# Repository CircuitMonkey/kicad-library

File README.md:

# kicad-library
CircuitMonkey's Custom KiCAD Library

Replaces FUGLY and poorly implemented KiCAD standard library symbols and footprints.

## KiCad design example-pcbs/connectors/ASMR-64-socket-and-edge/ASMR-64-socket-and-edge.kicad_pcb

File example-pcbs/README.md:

# kicad-library - example PCBs
Test and Validation boards for parts in CircuitMonkey's Custom KiCAD Library

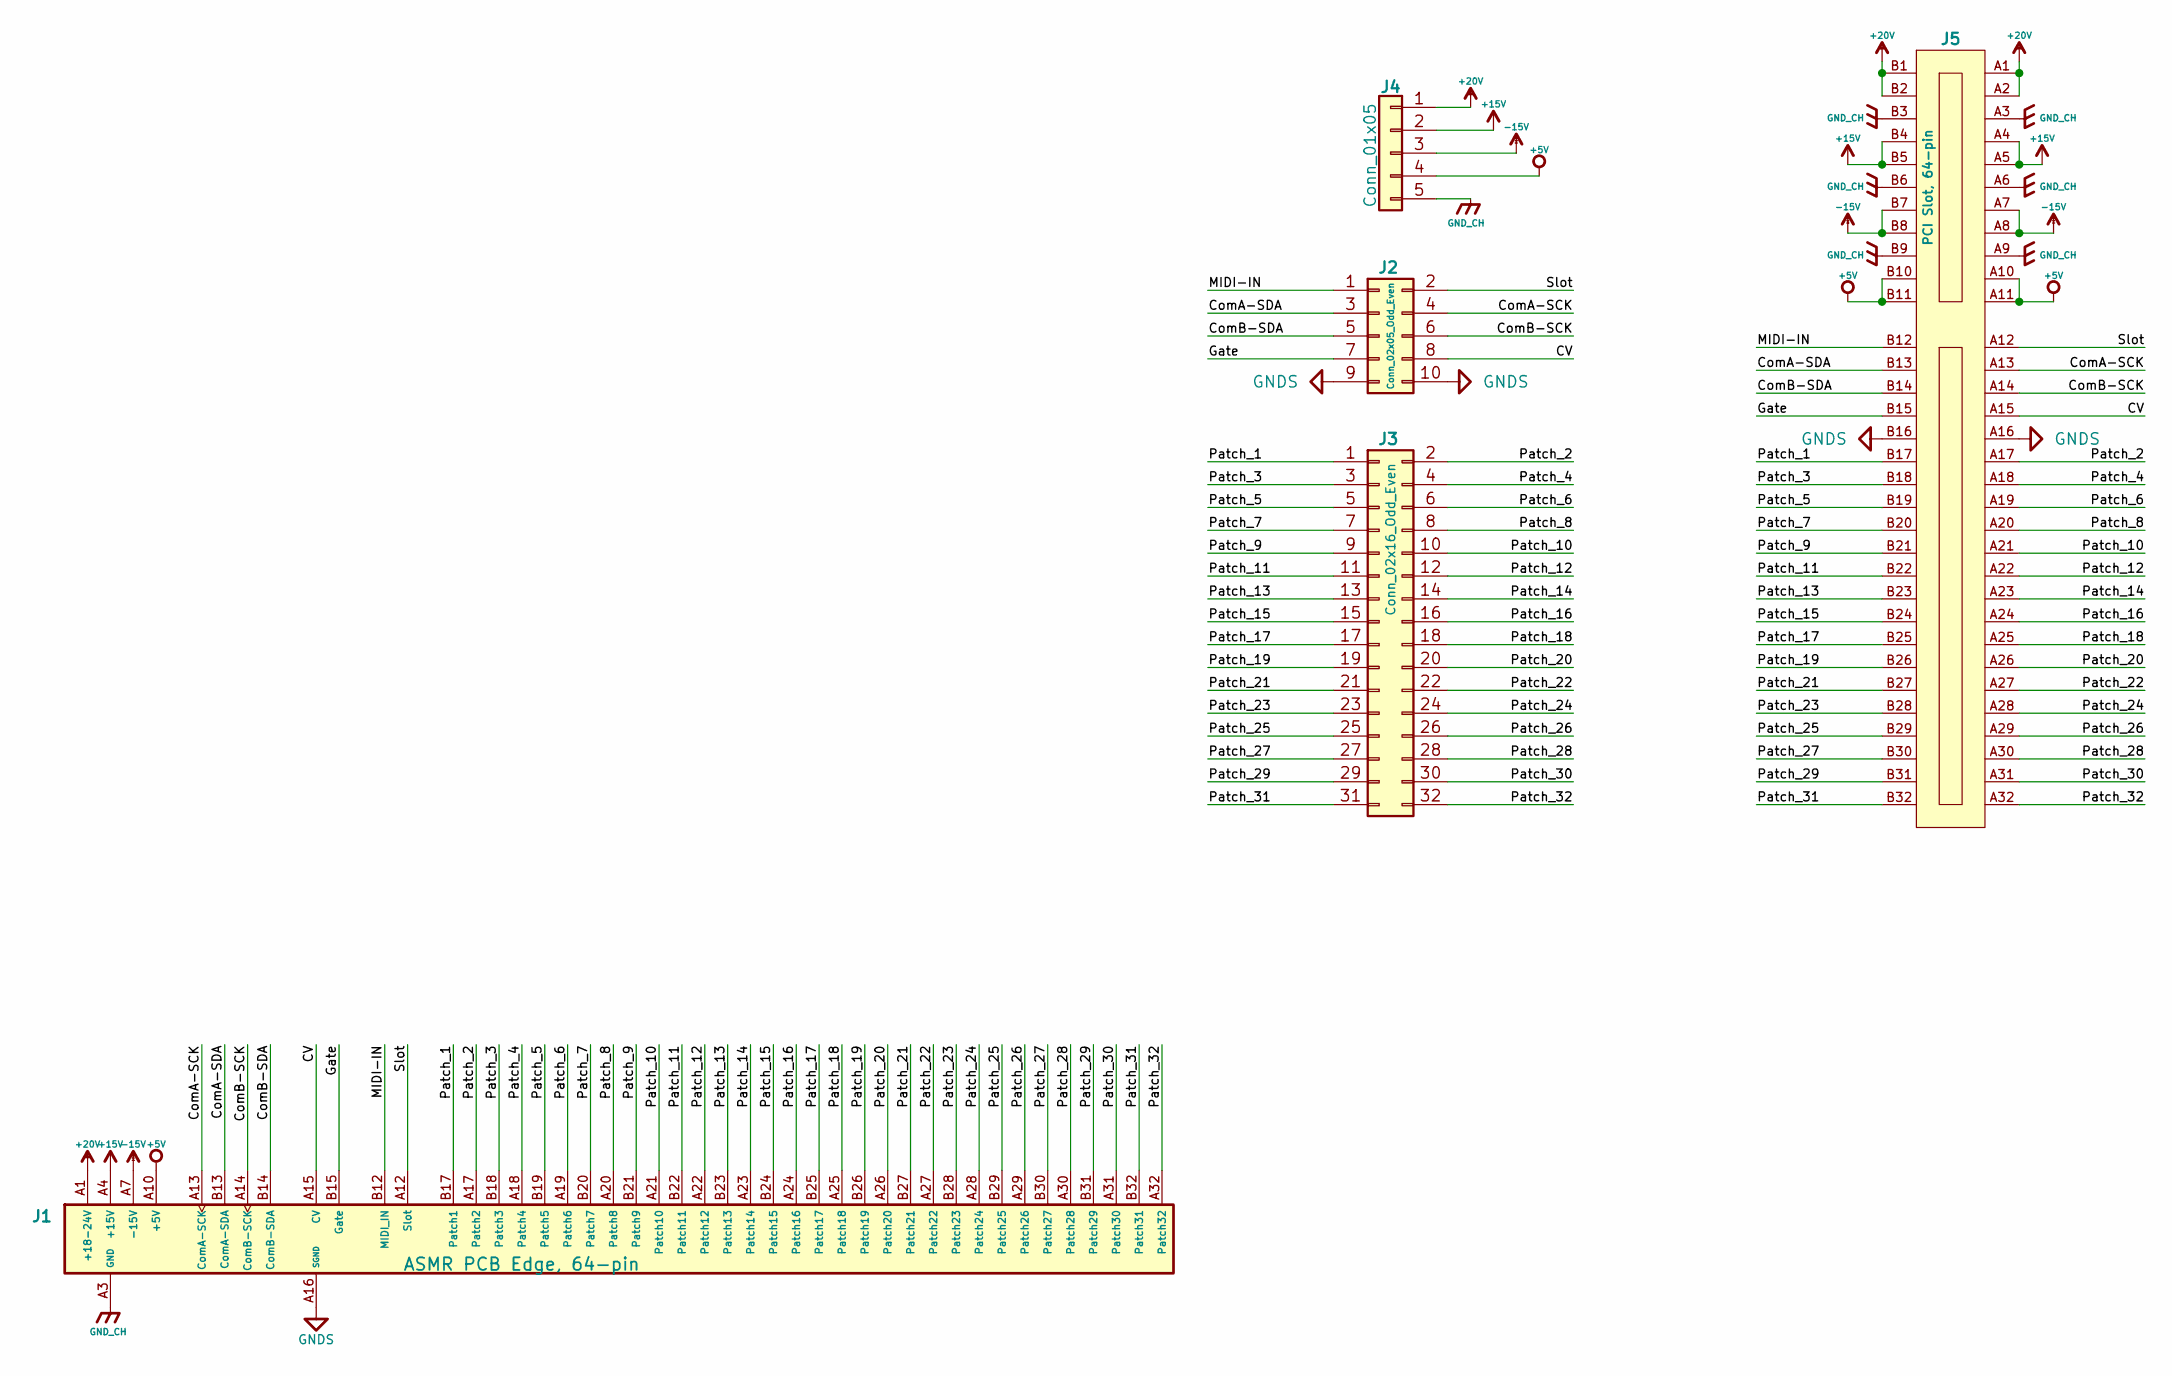
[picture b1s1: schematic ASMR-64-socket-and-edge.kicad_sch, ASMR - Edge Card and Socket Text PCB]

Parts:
J1: ASMR-Edge-64
J2: Conn_02x05_Odd_Even; PinHeader_2x05_P2.54mm_Vertical
J3: Conn_02x16_Odd_Even; PinHeader_2x16_P2.54mm_Vertical
J4: Conn_01x05; PinHeader_1x05_P2.54mm_Vertical
J5: PCI-Slot-64-THD-FCI-10018784; MPN 10018783-10201TLF

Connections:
+5V: J1.A10 (+5V), J1.A11 (+5V), J1.B10 (+5V), J1.B11 (+5V), J4.4, J5.A10, J5.A11, J5.B10, J5.B11
+15V: J1.A4 (+15V), J1.A5 (+15V), J1.B4 (+15V), J1.B5 (+15V), J4.2, J5.A4, J5.A5, J5.B4, J5.B5
+20V: J1.A1 (+18-24V), J1.A2 (+18-24V), J1.B1 (+18-24V), J1.B2 (+18-24V), J4.1, J5.A1, J5.A2, J5.B1, J5.B2
-15V: J1.A7 (-15V), J1.A8 (-15V), J1.B7 (-15V), J1.B8 (-15V), J4.3, J5.A7, J5.A8, J5.B7, J5.B8
/CV: J1.A15 (CV), J2.8, J5.A15
/ComA-SCK: J1.A13 (ComA-SCK), J2.4, J5.A13
/ComA-SDA: J1.B13 (ComA-SDA), J2.3, J5.B13
/ComB-SCK: J1.A14 (ComB-SCK), J2.6, J5.A14
/ComB-SDA: J1.B14 (ComB-SDA), J2.5, J5.B14
/Gate: J1.B15 (Gate), J2.7, J5.B15
/MIDI-IN: J1.B12 (MIDI_IN), J2.1, J5.B12
/Patch_1: J1.B17 (Patch1), J3.1, J5.B17
/Patch_2: J1.A17 (Patch2), J3.2, J5.A17
/Patch_3: J1.B18 (Patch3), J3.3, J5.B18
/Patch_4: J1.A18 (Patch4), J3.4, J5.A18
/Patch_5: J1.B19 (Patch5), J3.5, J5.B19
/Patch_6: J1.A19 (Patch6), J3.6, J5.A19
/Patch_7: J1.B20 (Patch7), J3.7, J5.B20
/Patch_8: J1.A20 (Patch8), J3.8, J5.A20
/Patch_9: J1.B21 (Patch9), J3.9, J5.B21
/Patch_10: J1.A21 (Patch10), J3.10, J5.A21
/Patch_11: J1.B22 (Patch11), J3.11, J5.B22
/Patch_12: J1.A22 (Patch12), J3.12, J5.A22
/Patch_13: J1.B23 (Patch13), J3.13, J5.B23
/Patch_14: J1.A23 (Patch14), J3.14, J5.A23
/Patch_15: J1.B24 (Patch15), J3.15, J5.B24
/Patch_16: J1.A24 (Patch16), J3.16, J5.A24
/Patch_17: J1.B25 (Patch17), J3.17, J5.B25
/Patch_18: J1.A25 (Patch18), J3.18, J5.A25
/Patch_19: J1.B26 (Patch19), J3.19, J5.B26
/Patch_20: J1.A26 (Patch20), J3.20, J5.A26
/Patch_21: J1.B27 (Patch21), J3.21, J5.B27
/Patch_22: J1.A27 (Patch22), J3.22, J5.A27
/Patch_23: J1.B28 (Patch23), J3.23, J5.B28
/Patch_24: J1.A28 (Patch24), J3.24, J5.A28
/Patch_25: J1.B29 (Patch25), J3.25, J5.B29
/Patch_26: J1.A29 (Patch26), J3.26, J5.A29
/Patch_27: J1.B30 (Patch27), J3.27, J5.B30
/Patch_28: J1.A30 (Patch28), J3.28, J5.A30
/Patch_29: J1.B31 (Patch29), J3.29, J5.B31
/Patch_30: J1.A31 (Patch30), J3.30, J5.A31
/Patch_31: J1.B32 (Patch31), J3.31, J5.B32
/Patch_32: J1.A32 (Patch32), J3.32, J5.A32
/Slot: J1.A12 (Slot), J2.2, J5.A12
GNDS: J1.A16 (SGND), J1.B16 (SGND), J2.9, J2.10, J5.A16, J5.B16
GND_CH: J1.A3 (GND), J1.A6 (GND), J1.A9 (GND), J1.B3 (GND), J1.B6 (GND), J1.B9 (GND), J4.5, J5.A3, J5.A6, J5.A9, J5.B3, J5.B6, J5.B9

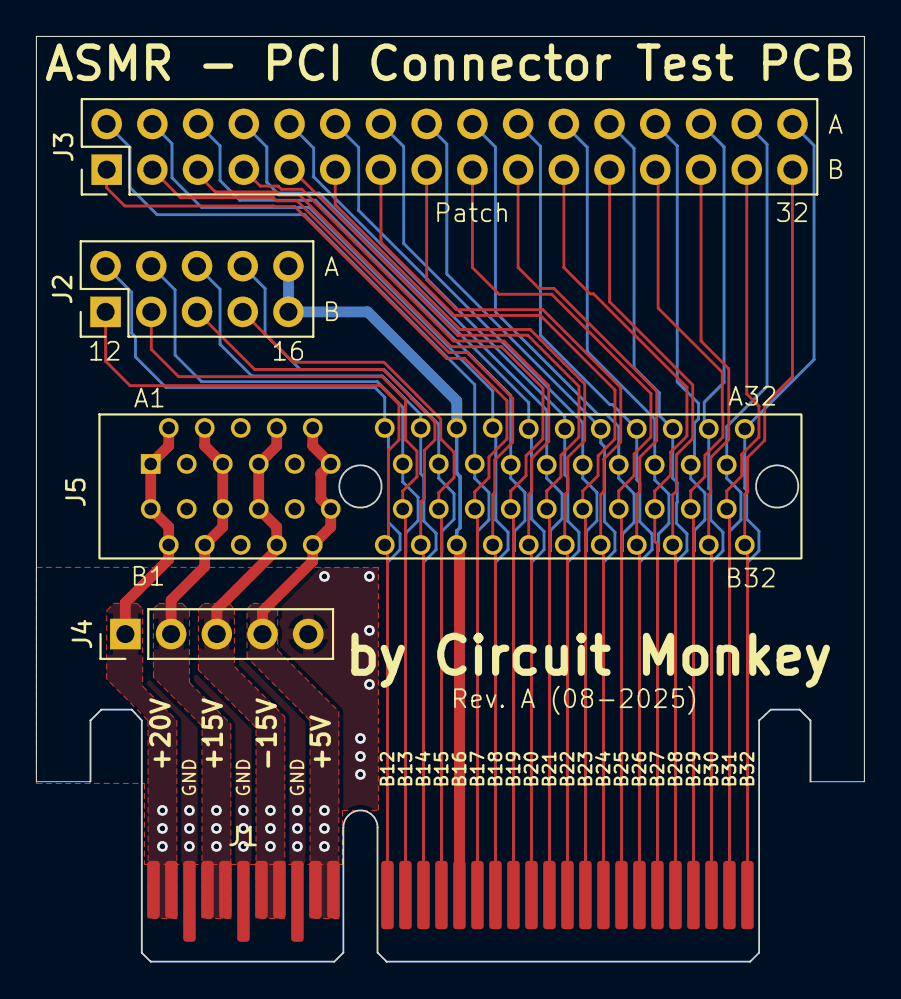
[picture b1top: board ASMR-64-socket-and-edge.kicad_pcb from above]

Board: 2 copper layers, 46.0 x 51.4 mm, 5 parts (0 on the bottom side), 46 nets.

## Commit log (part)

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2025-06-25 Fix issues with 3D model.
2025-06-25 Fix issues with footprint.
2025-06-25 Create breakout for 1/8 inch TRS jack.
2025-07-17 New Stuff!
2025-07-18 Fork KiCAD single logic gate symbol library.
2025-07-18 Add footprints to W65C816 chip.
2025-07-20 3D Models for osc. and QFN14
2025-07-20 Tune castelated pad.
2025-07-23 New 3D models for packages.
2025-07-23 New Symbols
2025-07-23 New Footprints
2025-07-25 Create SRAM component.
2025-07-25 Tune symbol for NAND gate and power block.
2025-07-26 Add some 3D models
2025-07-26 New CHIPz module footprints.
2025-07-26 Add 6530 CHIPz module symbol.
2025-07-27 Add KIM-1 KBD-Display footprint.
2025-07-27 Add Footprint for KIM1 KBD/Display
2025-07-27 Add KIM1 Control Symbol
2025-07-27 Add Control Module footprint.
2025-08-05 3D models added.
2025-08-05 Tune Symbol.
2025-08-05 Add SRN5040 inductor footprint.
2025-08-05 Tune castellated pads.
2025-08-05 KiCAD 0603 Resistor and Capacitor footprints were not good enough.
2025-08-05 Tune CPU module silkscreen.
2025-08-05 Tne RIOT module silkscreen.
2025-08-05 Tune KIM-1 Control module silkscreen.
2025-08-05 Tune KIM-1 Keyboard module footprint silkscreen.
2025-08-12 PCI Connector 3D Models
2025-08-12 New Footprints.
2025-08-12 New Symbols.
2025-08-12 Tune Resistor Symbol
2025-08-15 Add 64 pin PCI Connector
2025-08-15 Add USB PD support chip.
2025-08-15 Add new parts.
2025-08-16 Add 64 pin PCI connector.
2025-08-16 Add 64 pin PCI Edge for ASMR
2025-08-17 Update pad lengths on 64P ASMR PCI
2025-08-18 Test PCB for the ASMR Card Edge connectors.
2025-08-30 New Step models
2025-08-30 New Chip packages.
2025-08-30 Add some JST SH connectors.
2025-09-07 Add Diode Array 2-ch.
2025-09-07 Fix pin numbering error in package.
2025-11-04 Various changes and updates.
2026-01-14 Various updates.
